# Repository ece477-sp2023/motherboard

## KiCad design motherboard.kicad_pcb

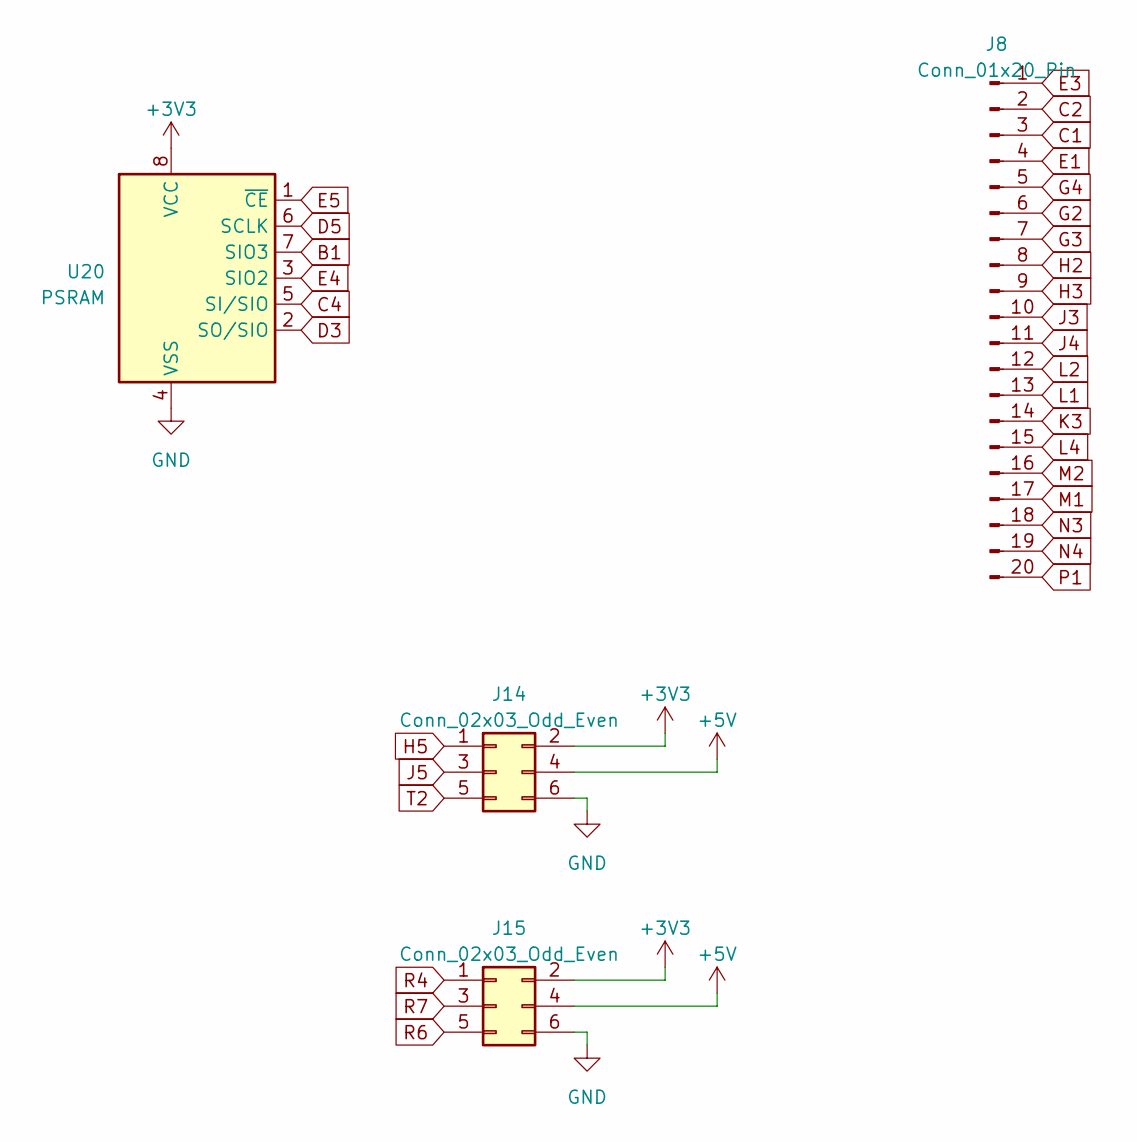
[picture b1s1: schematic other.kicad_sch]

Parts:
J8: Conn_01x20_Pin; PinHeader_2x10_P2.54mm_Vertical
J14, J15: Conn_02x03_Odd_Even; PinHeader_2x03_P2.54mm_Vertical
U20: PSRAM; SOIC-8_3.9x4.9mm_P1.27mm

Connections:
B1: U20.7 (SIO3); also elsewhere on the board
C1: J8.3; also elsewhere on the board
C2: J8.2; also elsewhere on the board
C4: U20.5 (SI/SIO); also elsewhere on the board
D3: U20.2 (SO/SIO); also elsewhere on the board
D5: U20.6 (SCLK); also elsewhere on the board
E1: J8.4; also elsewhere on the board
E3: J8.1; also elsewhere on the board
E4: U20.3 (SIO2); also elsewhere on the board
E5: U20.1 (~CE); also elsewhere on the board
G2: J8.6; also elsewhere on the board
G3: J8.7; also elsewhere on the board
G4: J8.5; also elsewhere on the board
H2: J8.8; also elsewhere on the board
H3: J8.9; also elsewhere on the board
H5: J14.1; also elsewhere on the board
J3: J8.10; also elsewhere on the board
J4: J8.11; also elsewhere on the board
J5: J14.3; also elsewhere on the board
K3: J8.14; also elsewhere on the board
L1: J8.13; also elsewhere on the board
L2: J8.12; also elsewhere on the board
L4: J8.15; also elsewhere on the board
M1: J8.17; also elsewhere on the board
M2: J8.16; also elsewhere on the board
N3: J8.18; also elsewhere on the board
N4: J8.19; also elsewhere on the board
P1: J8.20; also elsewhere on the board
R4: J15.1; also elsewhere on the board
R6: J15.5; also elsewhere on the board
R7: J15.3; also elsewhere on the board
T2: J14.5; also elsewhere on the board

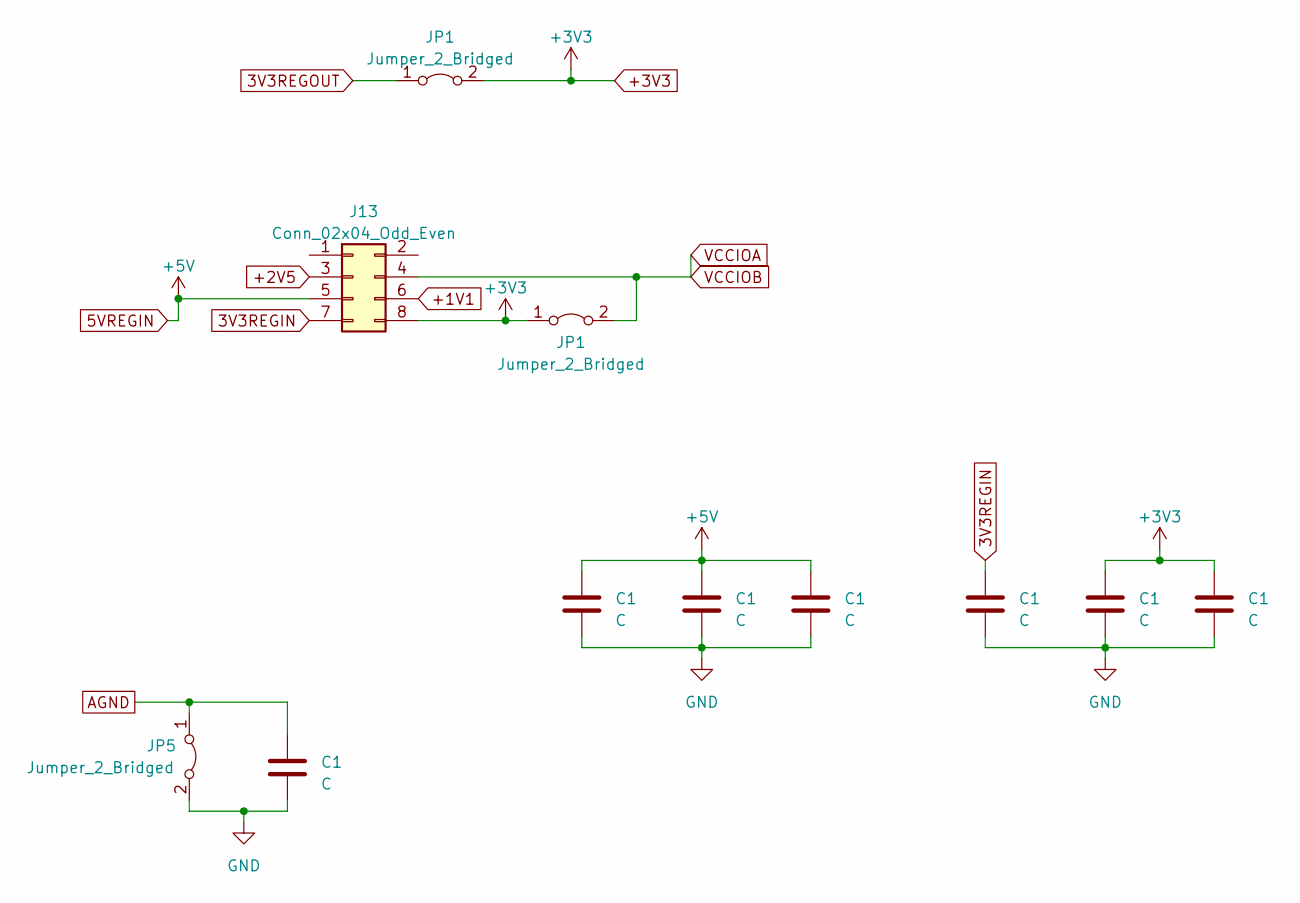
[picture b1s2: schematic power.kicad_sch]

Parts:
C1: C; C_0805_2012Metric
J13: Conn_02x04_Odd_Even; PinHeader_2x04_P2.54mm_Vertical
JP1, JP5: Jumper_2_Bridged; SolderJumper-2_P1.3mm_Bridged2Bar_RoundedPad1.0x1.5mm

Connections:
+1V1: J13.6; also elsewhere on the board
+2V5: J13.3; also elsewhere on the board

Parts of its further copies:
C2, C3, C4, C5, C6, C7: C; C_0805_2012Metric
JP3, JP4: Jumper_2_Bridged; SolderJumper-2_P1.3mm_Bridged2Bar_RoundedPad1.0x1.5mm

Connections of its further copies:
3V3REGOUT: JP4.1 (A); also elsewhere on the board

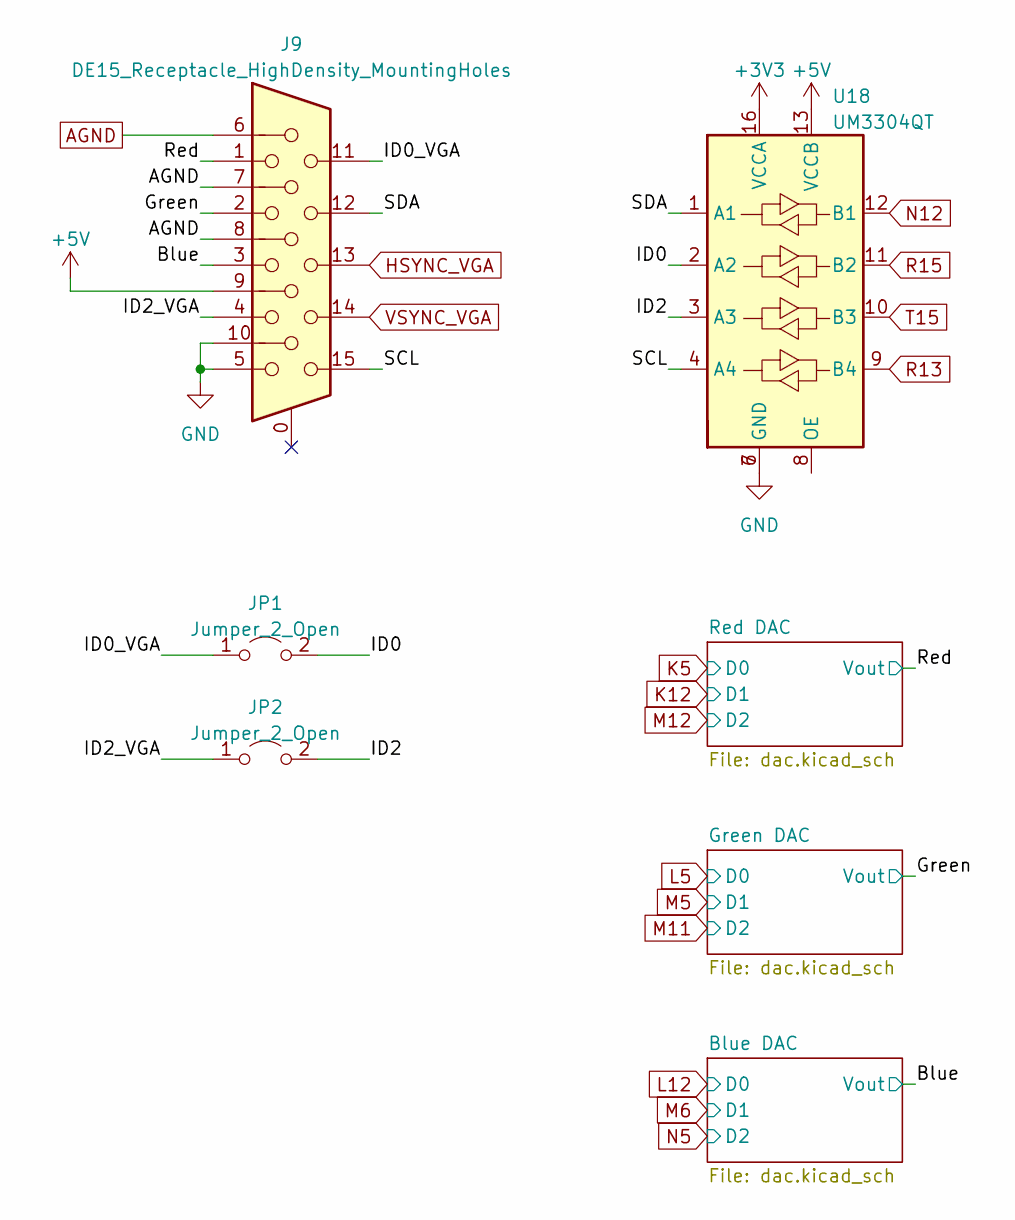
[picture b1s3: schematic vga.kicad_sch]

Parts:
J9: DE15_Receptacle_HighDensity_MountingHoles; DSUB-15-HD_Female_Horizontal_P2.29x1.98mm_EdgePinOffset3.03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
JP1, JP2: Jumper_2_Open; SolderJumper-2_P1.3mm_Open_TrianglePad1.0x1.5mm
U18: UM3304QT; QFN-16_1.8x2.6_Pitch0.4mm

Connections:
/VGA/Blue: J9.3; also elsewhere on the board
/VGA/Green: J9.2; also elsewhere on the board
/VGA/ID2_VGA: J9.4, JP2.1 (A)
/Voltage Shifting/5V Data: U18.10 (B3); also elsewhere on the board
OE: U18.8 (OE); also elsewhere on the board

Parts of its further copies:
U19: UM3304QT; QFN-16_1.8x2.6_Pitch0.4mm

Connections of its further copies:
N12: U19.12 (B1); also elsewhere on the board
R13: U19.9 (B4); also elsewhere on the board
R15: U19.11 (B2); also elsewhere on the board
T15: U19.10 (B3); also elsewhere on the board

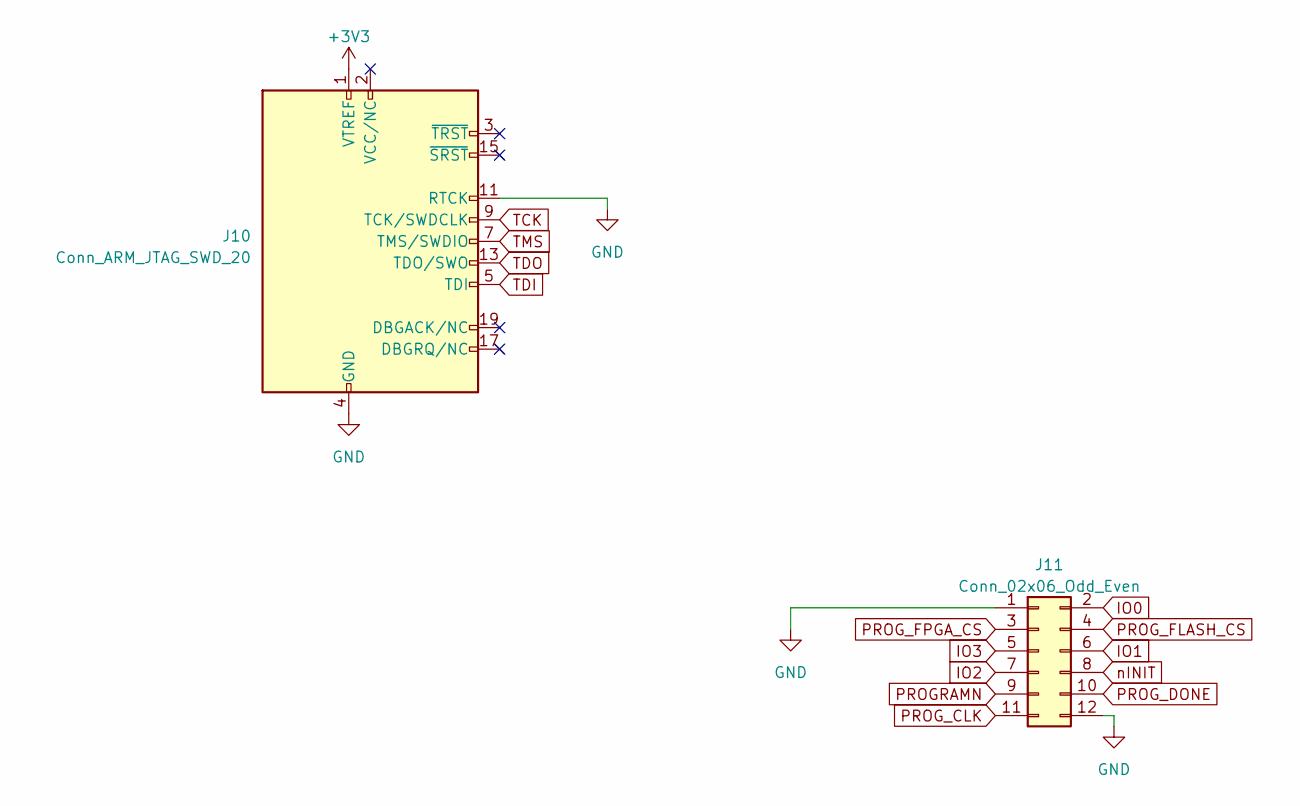
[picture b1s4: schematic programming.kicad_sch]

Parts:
J10: Conn_ARM_JTAG_SWD_20; PinHeader_2x10_P2.54mm_Vertical
J11: Conn_02x06_Odd_Even; PinHeader_2x06_P2.54mm_Vertical

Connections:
IO0: J11.2; also elsewhere on the board
IO1: J11.6; also elsewhere on the board
IO2: J11.7; also elsewhere on the board
IO3: J11.5; also elsewhere on the board
PROGRAMN: J11.9; also elsewhere on the board
PROG_CLK: J11.11; also elsewhere on the board
PROG_DONE: J11.10; also elsewhere on the board
PROG_FLASH_CS: J11.4; also elsewhere on the board
PROG_FPGA_CS: J11.3; also elsewhere on the board
TCK: J10.9 (TCK/SWDCLK); also elsewhere on the board
TDI: J10.5 (TDI); also elsewhere on the board
TDO: J10.13 (TDO/SWO); also elsewhere on the board
TMS: J10.7 (TMS/SWDIO); also elsewhere on the board
nINIT: J11.8; also elsewhere on the board

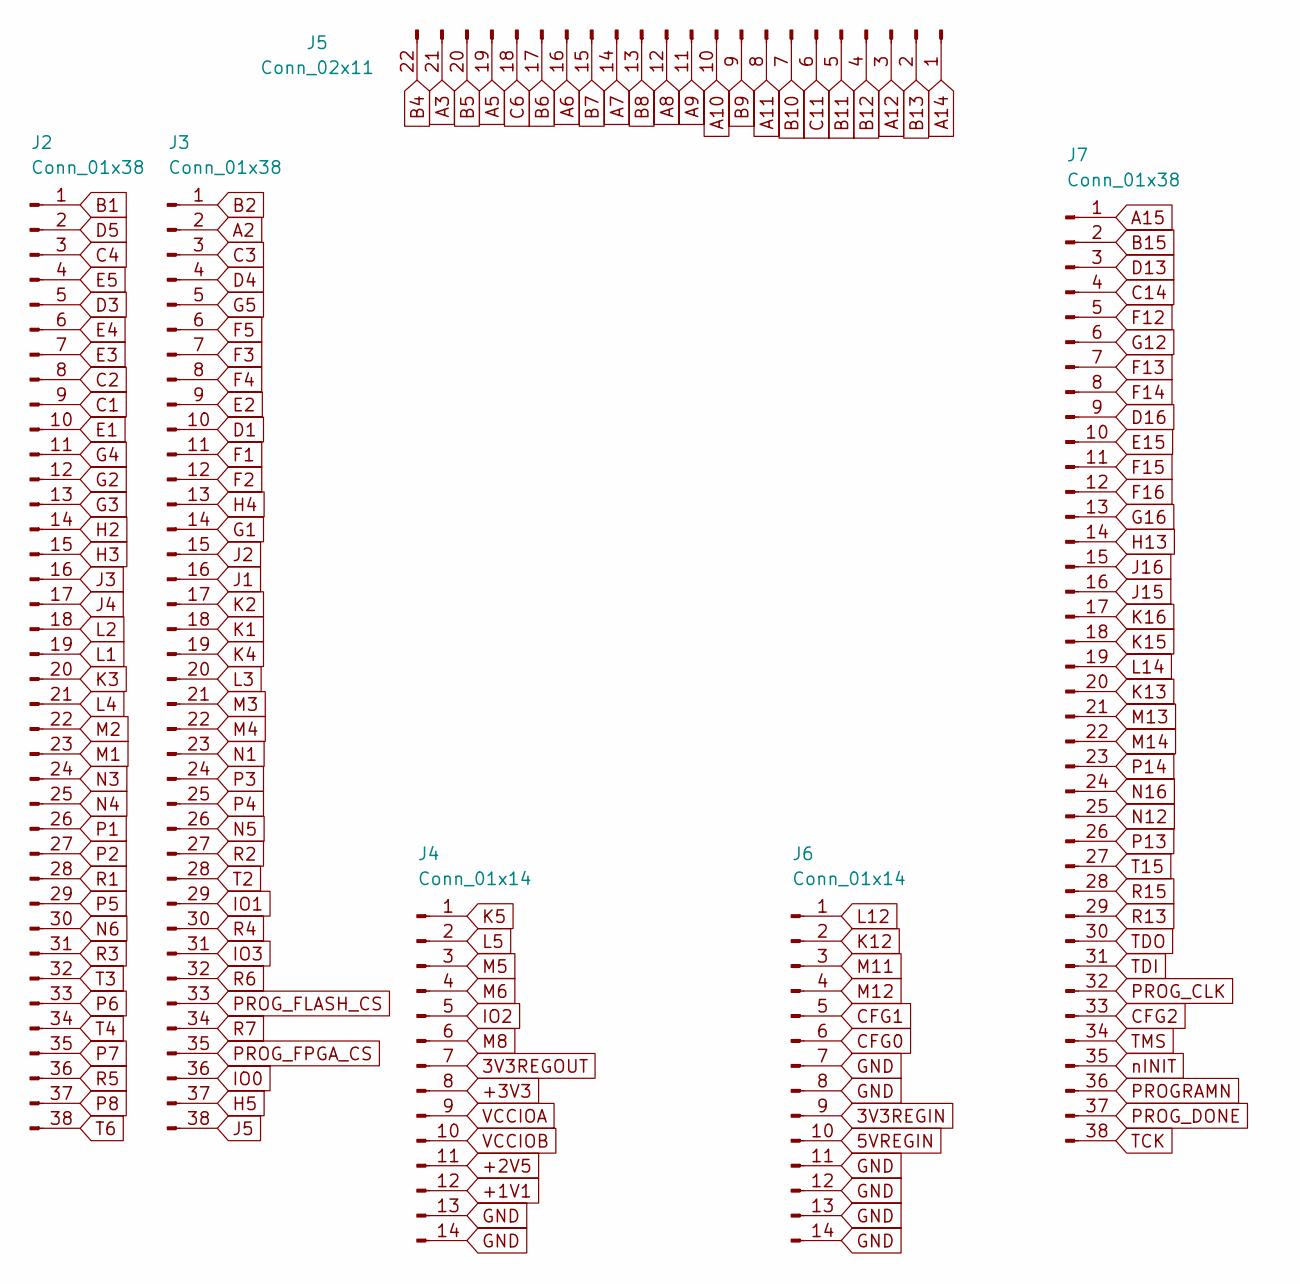
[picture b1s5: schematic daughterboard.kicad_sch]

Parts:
J2: Conn_01x38; PinHeader_1x38_P1.27mm_Vertical
J3, J7: Conn_01x38; PinHeader_2x19_P2.54mm_Vertical
J4, J6: Conn_01x14; PinHeader_2x07_P2.54mm_Vertical
J5: Conn_02x11; PinHeader_2x11_P2.54mm_Vertical

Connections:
3V3REGOUT: J4.7; also elsewhere on the board
+1V1: J4.12; also elsewhere on the board
+2V5: J4.11; also elsewhere on the board
A2: J3.2; also elsewhere on the board
A3: J5.21; also elsewhere on the board
A5: J5.19; also elsewhere on the board
A6: J5.16; also elsewhere on the board
A7: J5.14; also elsewhere on the board
A8: J5.12; also elsewhere on the board
A9: J5.11; also elsewhere on the board
A10: J5.10; also elsewhere on the board
A11: J5.8; also elsewhere on the board
A12: J5.3; also elsewhere on the board
A14: J5.1; also elsewhere on the board
A15: J7.1; also elsewhere on the board
B1: J2.1; also elsewhere on the board
B2: J3.1; also elsewhere on the board
B4: J5.22; also elsewhere on the board
B5: J5.20; also elsewhere on the board
B6: J5.17; also elsewhere on the board
B7: J5.15; also elsewhere on the board
B8: J5.13; also elsewhere on the board
B9: J5.9; also elsewhere on the board
B10: J5.7; also elsewhere on the board
B11: J5.5; also elsewhere on the board
B12: J5.4; also elsewhere on the board
B13: J5.2; also elsewhere on the board
B15: J7.2; also elsewhere on the board
C1: J2.9; also elsewhere on the board
C2: J2.8; also elsewhere on the board
C3: J3.3; also elsewhere on the board
C4: J2.3; also elsewhere on the board
C6: J5.18; also elsewhere on the board
C11: J5.6; also elsewhere on the board
C14: J7.4; also elsewhere on the board
CFG0: J6.6
CFG1: J6.5
CFG2: J7.33
D1: J3.10; also elsewhere on the board
D3: J2.5; also elsewhere on the board
D4: J3.4; also elsewhere on the board
D5: J2.2; also elsewhere on the board
D13: J7.3; also elsewhere on the board
D16: J7.9; also elsewhere on the board
E1: J2.10; also elsewhere on the board
E2: J3.9; also elsewhere on the board
E3: J2.7; also elsewhere on the board
E4: J2.6; also elsewhere on the board
E5: J2.4; also elsewhere on the board
F1: J3.11; also elsewhere on the board
F2: J3.12; also elsewhere on the board
F3: J3.7; also elsewhere on the board
F4: J3.8; also elsewhere on the board
F5: J3.6; also elsewhere on the board
F12: J7.5; also elsewhere on the board
F13: J7.7; also elsewhere on the board
F15: J7.11; also elsewhere on the board
G1: J3.14; also elsewhere on the board
G2: J2.12; also elsewhere on the board
G3: J2.13; also elsewhere on the board
G4: J2.11; also elsewhere on the board
G5: J3.5; also elsewhere on the board
G16: J7.13; also elsewhere on the board
H2: J2.14; also elsewhere on the board
H3: J2.15; also elsewhere on the board
H4: J3.13; also elsewhere on the board
H5: J3.37; also elsewhere on the board
H13: J7.14; also elsewhere on the board
IO0: J3.36; also elsewhere on the board
IO1: J3.29; also elsewhere on the board
IO2: J4.5; also elsewhere on the board
IO3: J3.31; also elsewhere on the board
J1: J3.16; also elsewhere on the board
J2: J3.15; also elsewhere on the board
J3: J2.16; also elsewhere on the board
J4: J2.17; also elsewhere on the board
J5: J3.38; also elsewhere on the board
J15: J7.16; also elsewhere on the board
J16: J7.15; also elsewhere on the board
K1: J3.18; also elsewhere on the board
K2: J3.17; also elsewhere on the board
K3: J2.20; also elsewhere on the board
K4: J3.19; also elsewhere on the board
K5: J4.1; also elsewhere on the board
K13: J7.20; also elsewhere on the board
K15: J7.18; also elsewhere on the board
K16: J7.17; also elsewhere on the board
L1: J2.19; also elsewhere on the board
L2: J2.18; also elsewhere on the board
L3: J3.20; also elsewhere on the board
L4: J2.21; also elsewhere on the board
L5: J4.2; also elsewhere on the board
L12: J6.1; also elsewhere on the board
L14: J7.19; also elsewhere on the board
M1: J2.23; also elsewhere on the board
M2: J2.22; also elsewhere on the board
M3: J3.21; also elsewhere on the board
M4: J3.22; also elsewhere on the board
M5: J4.3; also elsewhere on the board
M6: J4.4; also elsewhere on the board
M8: J4.6
M11: J6.3; also elsewhere on the board
M12: J6.4; also elsewhere on the board
M13: J7.21; also elsewhere on the board
M14: J7.22; also elsewhere on the board
N1: J3.23; also elsewhere on the board
N3: J2.24; also elsewhere on the board
N4: J2.25; also elsewhere on the board
N5: J3.26; also elsewhere on the board
N6: J2.30
N12: J7.25; also elsewhere on the board
N16: J7.24; also elsewhere on the board
OE: J3.27; also elsewhere on the board
P1: J2.26; also elsewhere on the board
P2: J2.27
P3: J3.24; also elsewhere on the board
P4: J3.25; also elsewhere on the board
P5: J2.29
P6: J2.33
P7: J2.35
P8: J2.37
P13: J7.26; also elsewhere on the board
P14: J7.23; also elsewhere on the board
PROGRAMN: J7.36; also elsewhere on the board
PROG_CLK: J7.32; also elsewhere on the board
PROG_DONE: J7.37; also elsewhere on the board
PROG_FLASH_CS: J3.33; also elsewhere on the board
PROG_FPGA_CS: J3.35; also elsewhere on the board
R1: J2.28
R3: J2.31
R4: J3.30; also elsewhere on the board
R5: J2.36
R6: J3.32; also elsewhere on the board
R7: J3.34; also elsewhere on the board
R13: J7.29; also elsewhere on the board
R15: J7.28; also elsewhere on the board
T2: J3.28; also elsewhere on the board
T3: J2.32
T4: J2.34
T6: J2.38
T15: J7.27; also elsewhere on the board
TCK: J7.38; also elsewhere on the board
TDI: J7.31; also elsewhere on the board
TDO: J7.30; also elsewhere on the board
TMS: J7.34; also elsewhere on the board
nINIT: J7.35; also elsewhere on the board

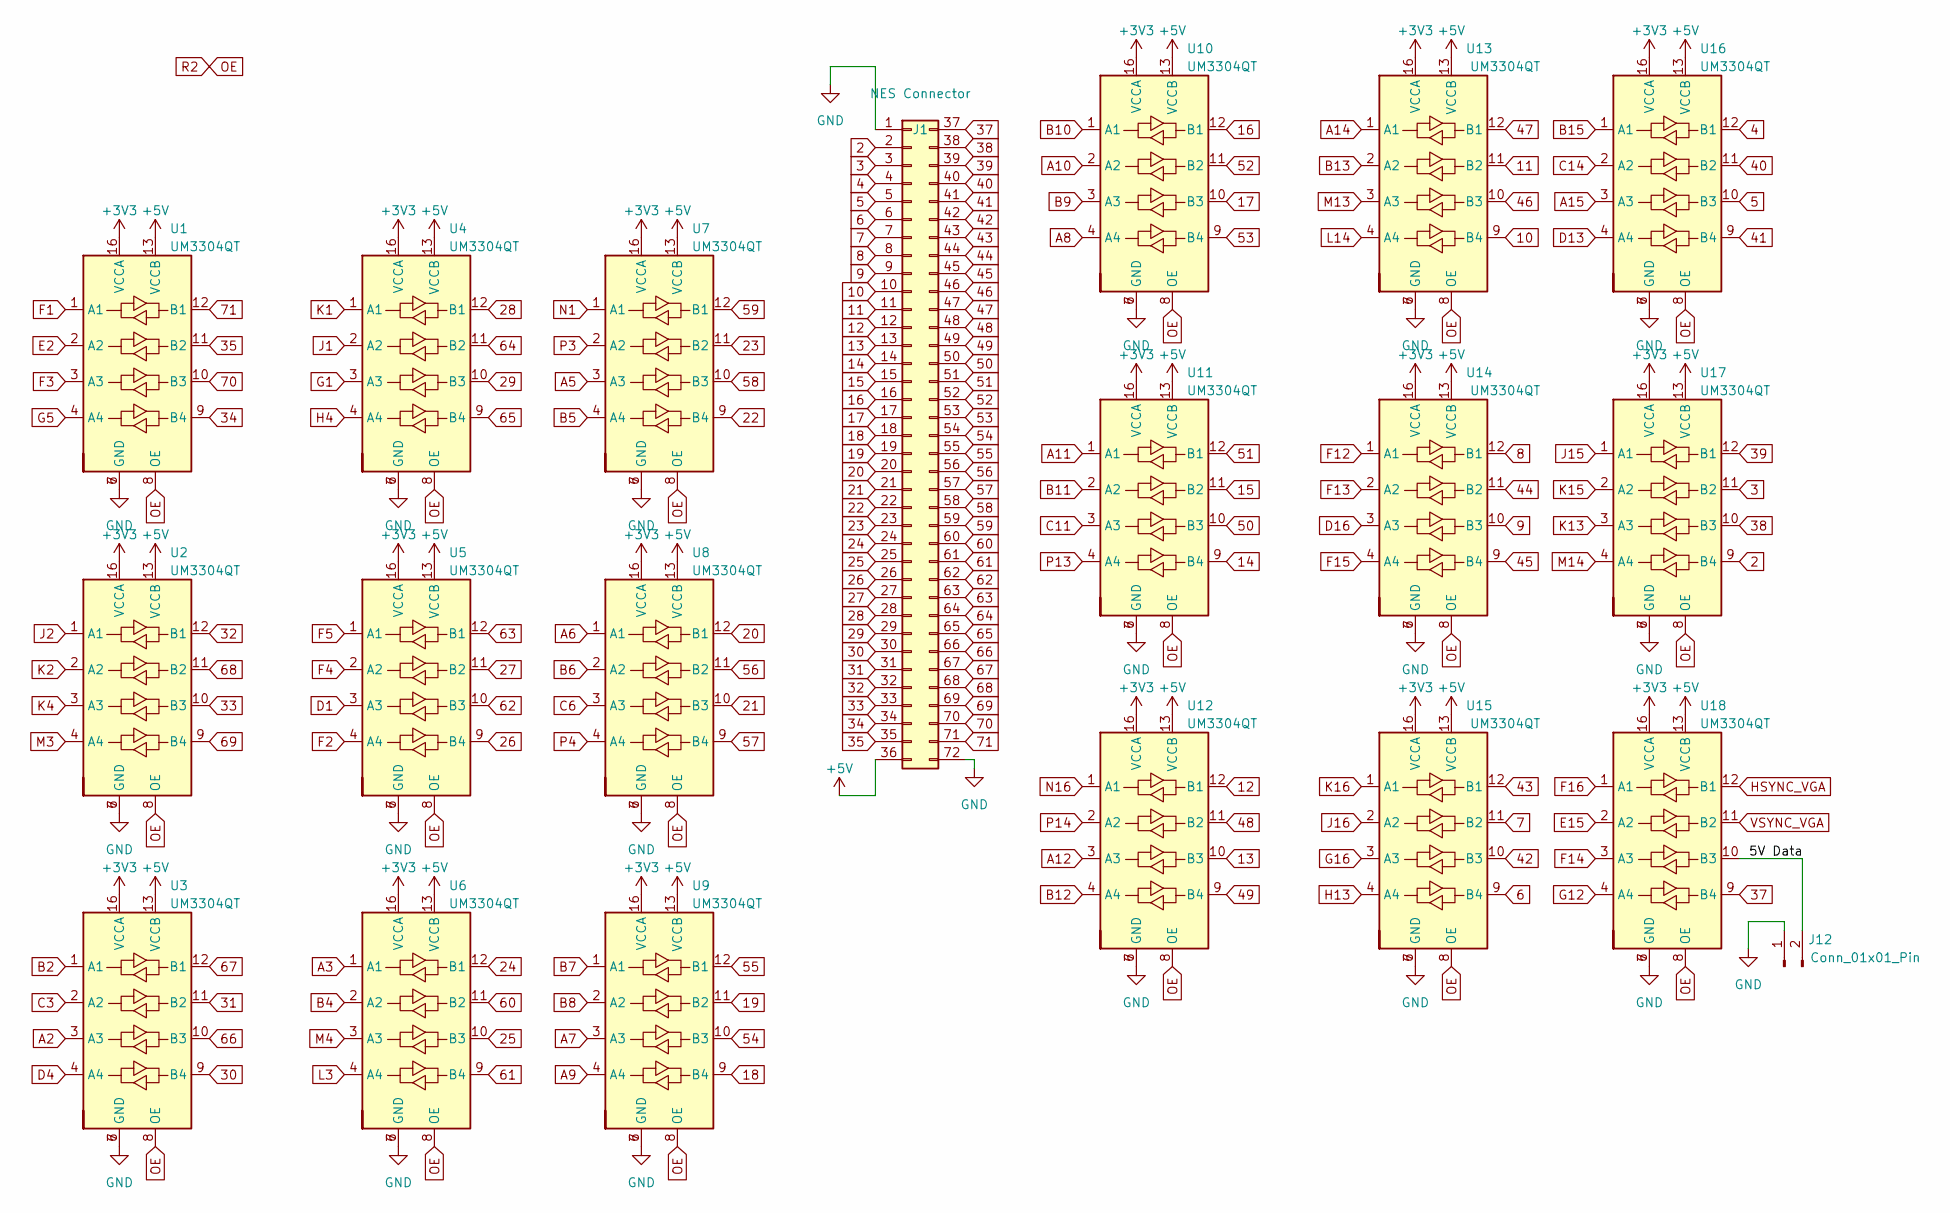
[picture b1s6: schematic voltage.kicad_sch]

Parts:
J1: NES Connector; NES_Connector
J12: Conn_01x01_Pin; PinHeader_1x02_P2.54mm_Vertical
U1, U2, U3, U4, U5, U6, U7, U8, U9, U10, U11, U12, U13, U14, U15, U16, U17, U18: UM3304QT; QFN-16_1.8x2.6_Pitch0.4mm

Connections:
2: J1.2, U17.9 (B4)
3: J1.3, U17.11 (B2)
4: J1.4, U16.12 (B1)
5: J1.5, U16.10 (B3)
6: J1.6, U15.9 (B4)
7: J1.7, U15.11 (B2)
8: J1.8, U14.12 (B1)
9: J1.9, U14.10 (B3)
10: J1.10, U13.9 (B4)
11: J1.11, U13.11 (B2)
12: J1.12, U12.12 (B1)
13: J1.13, U12.10 (B3)
14: J1.14, U11.9 (B4)
15: J1.15, U11.11 (B2)
16: J1.16, U10.12 (B1)
17: J1.17, U10.10 (B3)
18: J1.18, U9.9 (B4)
19: J1.19, U9.11 (B2)
20: J1.20, U8.12 (B1)
21: J1.21, U8.10 (B3)
22: J1.22, U7.9 (B4)
23: J1.23, U7.11 (B2)
24: J1.24, U6.12 (B1)
25: J1.25, U6.10 (B3)
26: J1.26, U5.9 (B4)
27: J1.27, U5.11 (B2)
28: J1.28, U4.12 (B1)
29: J1.29, U4.10 (B3)
30: J1.30, U3.9 (B4)
31: J1.31, U3.11 (B2)
32: J1.32, U2.12 (B1)
33: J1.33, U2.10 (B3)
34: J1.34, U1.9 (B4)
35: J1.35, U1.11 (B2)
38: J1.38, U17.10 (B3)
39: J1.39, U17.12 (B1)
40: J1.40, U16.11 (B2)
41: J1.41, U16.9 (B4)
42: J1.42, U15.10 (B3)
43: J1.43, U15.12 (B1)
44: J1.44, U14.11 (B2)
45: J1.45, U14.9 (B4)
46: J1.46, U13.10 (B3)
47: J1.47, U13.12 (B1)
48: J1.48, U12.11 (B2)
49: J1.49, U12.9 (B4)
50: J1.50, U11.10 (B3)
51: J1.51, U11.12 (B1)
52: J1.52, U10.11 (B2)
53: J1.53, U10.9 (B4)
54: J1.54, U9.10 (B3)
55: J1.55, U9.12 (B1)
56: J1.56, U8.11 (B2)
57: J1.57, U8.9 (B4)
58: J1.58, U7.10 (B3)
59: J1.59, U7.12 (B1)
60: J1.60, U6.11 (B2)
61: J1.61, U6.9 (B4)
62: J1.62, U5.10 (B3)
63: J1.63, U5.12 (B1)
64: J1.64, U4.11 (B2)
65: J1.65, U4.9 (B4)
66: J1.66, U3.10 (B3)
67: J1.67, U3.12 (B1)
68: J1.68, U2.11 (B2)
69: J1.69, U2.9 (B4)
70: J1.70, U1.10 (B3)
71: J1.71, U1.12 (B1)
/Voltage Shifting/5V Data: J12.2, U18.10 (B3)
A2: U3.3 (A3); also elsewhere on the board
A3: U6.1 (A1); also elsewhere on the board
A5: U7.3 (A3); also elsewhere on the board
A6: U8.1 (A1); also elsewhere on the board
A7: U9.3 (A3); also elsewhere on the board
A8: U10.4 (A4); also elsewhere on the board
A9: U9.4 (A4); also elsewhere on the board
A10: U10.2 (A2); also elsewhere on the board
A11: U11.1 (A1); also elsewhere on the board
A12: U12.3 (A3); also elsewhere on the board
A14: U13.1 (A1); also elsewhere on the board
A15: U16.3 (A3); also elsewhere on the board
B2: U3.1 (A1); also elsewhere on the board
B4: U6.2 (A2); also elsewhere on the board
B5: U7.4 (A4); also elsewhere on the board
B6: U8.2 (A2); also elsewhere on the board
B7: U9.1 (A1); also elsewhere on the board
B8: U9.2 (A2); also elsewhere on the board
B9: U10.3 (A3); also elsewhere on the board
B10: U10.1 (A1); also elsewhere on the board
B11: U11.2 (A2); also elsewhere on the board
B12: U12.4 (A4); also elsewhere on the board
B13: U13.2 (A2); also elsewhere on the board
B15: U16.1 (A1); also elsewhere on the board
C3: U3.2 (A2); also elsewhere on the board
C6: U8.3 (A3); also elsewhere on the board
C11: U11.3 (A3); also elsewhere on the board
C14: U16.2 (A2); also elsewhere on the board
D1: U5.3 (A3); also elsewhere on the board
D4: U3.4 (A4); also elsewhere on the board
D13: U16.4 (A4); also elsewhere on the board
D16: U14.3 (A3); also elsewhere on the board
E2: U1.2 (A2); also elsewhere on the board
F1: U1.1 (A1); also elsewhere on the board
F2: U5.4 (A4); also elsewhere on the board
F3: U1.3 (A3); also elsewhere on the board
F4: U5.2 (A2); also elsewhere on the board
F5: U5.1 (A1); also elsewhere on the board
F12: U14.1 (A1); also elsewhere on the board
F13: U14.2 (A2); also elsewhere on the board
F15: U14.4 (A4); also elsewhere on the board
G1: U4.3 (A3); also elsewhere on the board
G5: U1.4 (A4); also elsewhere on the board
G16: U15.3 (A3); also elsewhere on the board
H4: U4.4 (A4); also elsewhere on the board
H13: U15.4 (A4); also elsewhere on the board
J1: U4.2 (A2); also elsewhere on the board
J2: U2.1 (A1); also elsewhere on the board
J15: U17.1 (A1); also elsewhere on the board
J16: U15.2 (A2); also elsewhere on the board
K1: U4.1 (A1); also elsewhere on the board
K2: U2.2 (A2); also elsewhere on the board
K4: U2.3 (A3); also elsewhere on the board
K13: U17.3 (A3); also elsewhere on the board
K15: U17.2 (A2); also elsewhere on the board
K16: U15.1 (A1); also elsewhere on the board
L3: U6.4 (A4); also elsewhere on the board
L14: U13.4 (A4); also elsewhere on the board
M3: U2.4 (A4); also elsewhere on the board
M4: U6.3 (A3); also elsewhere on the board
M13: U13.3 (A3); also elsewhere on the board
M14: U17.4 (A4); also elsewhere on the board
N1: U7.1 (A1); also elsewhere on the board
N16: U12.1 (A1); also elsewhere on the board
OE: U1.8 (OE), U2.8 (OE), U3.8 (OE), U4.8 (OE), U5.8 (OE), U6.8 (OE), U7.8 (OE), U8.8 (OE), U9.8 (OE), U10.8 (OE), U11.8 (OE), U12.8 (OE), U13.8 (OE), U14.8 (OE), U15.8 (OE), U16.8 (OE), U17.8 (OE), U18.8 (OE); also elsewhere on the board
P3: U7.2 (A2); also elsewhere on the board
P4: U8.4 (A4); also elsewhere on the board
P13: U11.4 (A4); also elsewhere on the board
P14: U12.2 (A2); also elsewhere on the board

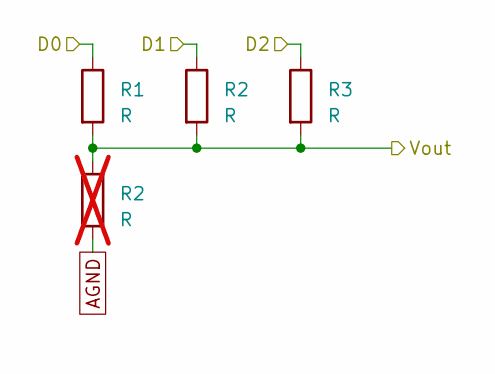
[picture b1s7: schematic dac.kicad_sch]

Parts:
R1, R3: R; R_0805_2012Metric
R2: R; R_0805_2012Metric; not fitted

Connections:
K5: R1.1; also elsewhere on the board
M12: R3.1; also elsewhere on the board

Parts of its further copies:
R5, R7, R8, R12, R13: R; R_0805_2012Metric; not fitted
R6, R9, R11, R14: R; R_0805_2012Metric

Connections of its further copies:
/VGA/Blue: R11.2, R12.1, R13.2, R14.2; also elsewhere on the board
/VGA/Green: R6.2, R7.1, R8.2, R9.2; also elsewhere on the board
L5: R6.1; also elsewhere on the board
L12: R11.1; also elsewhere on the board
M5: R8.1; also elsewhere on the board
M6: R13.1; also elsewhere on the board
M11: R9.1; also elsewhere on the board
N5: R14.1; also elsewhere on the board

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
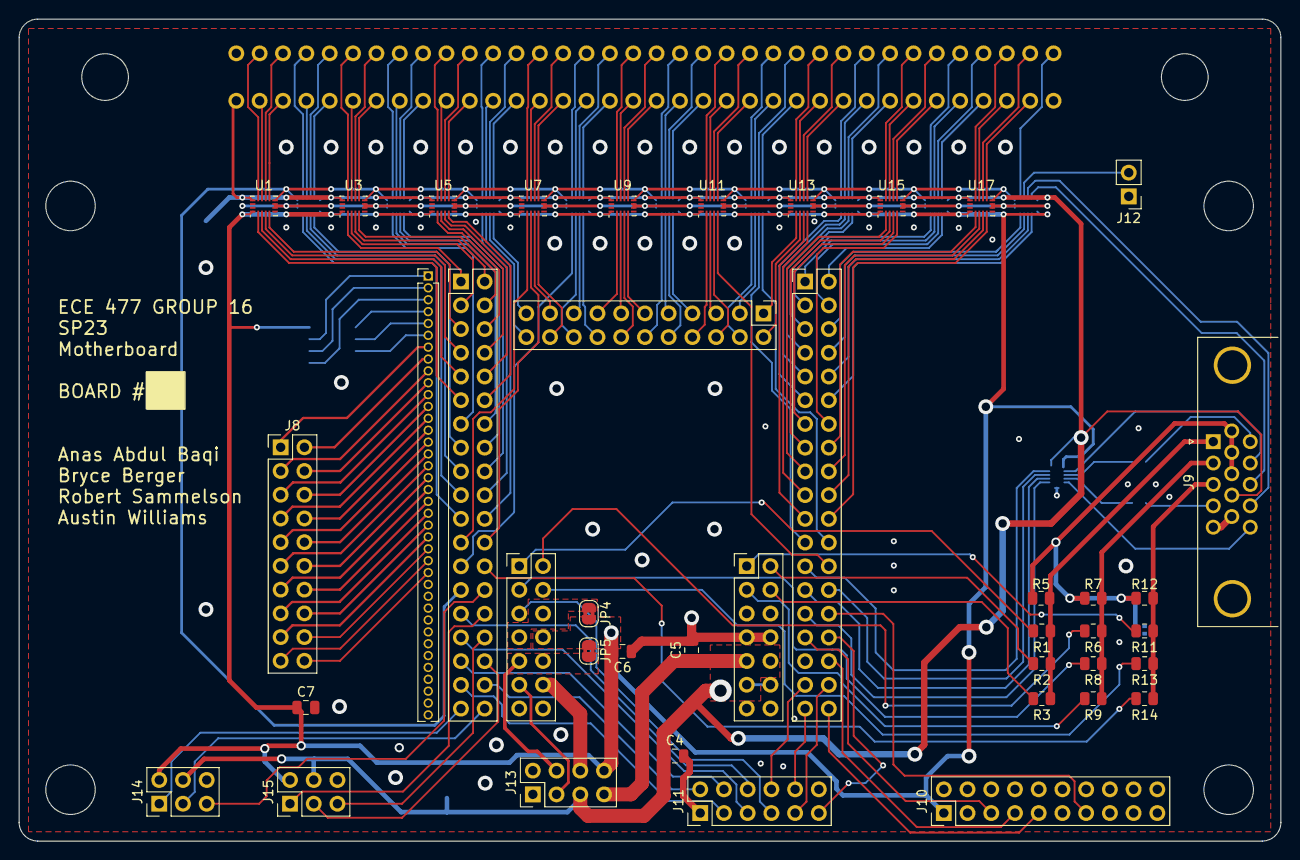
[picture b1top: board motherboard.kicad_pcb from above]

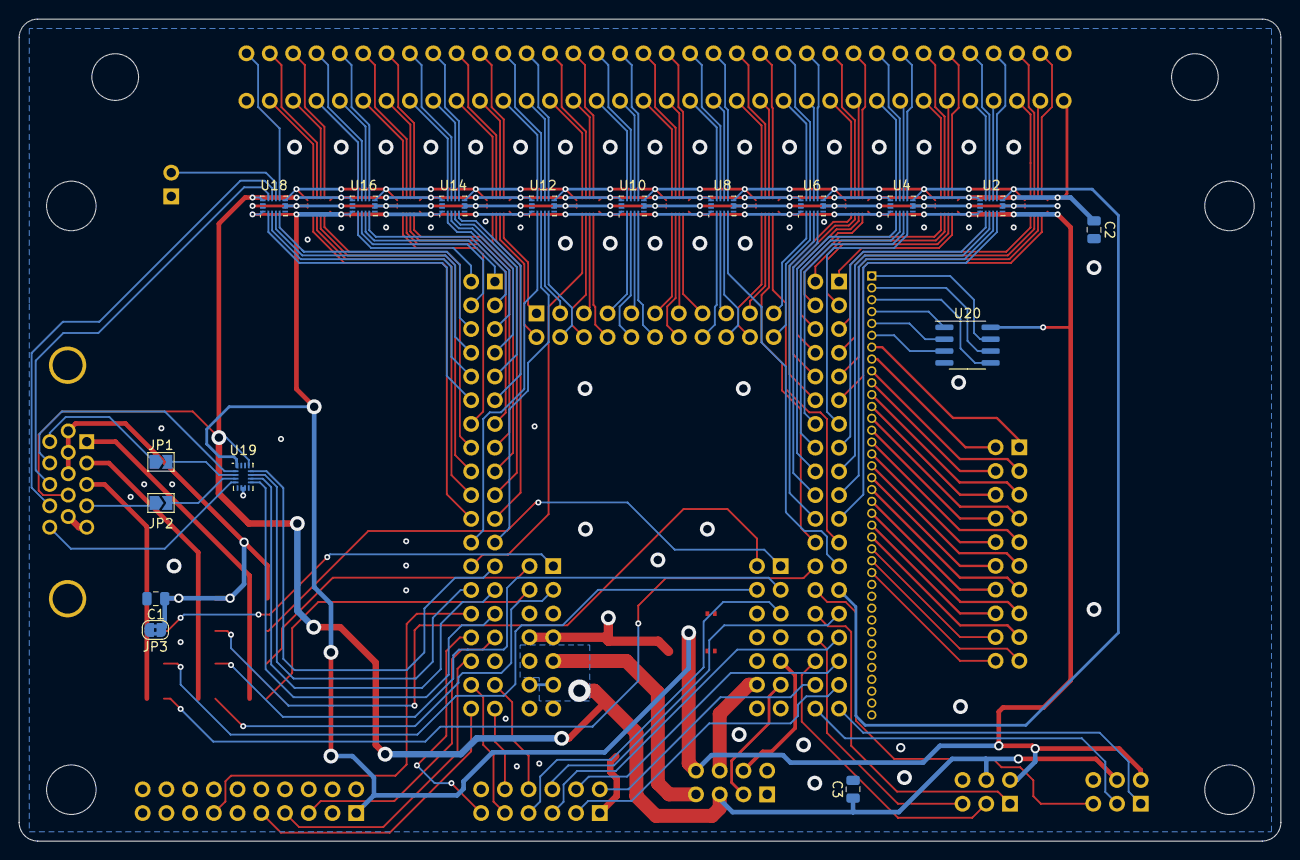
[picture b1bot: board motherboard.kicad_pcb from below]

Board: 2 copper layers, 135.1 x 88.0 mm, 59 parts (17 on the bottom side), 222 nets.

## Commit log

2023-03-09 Voltage conversion routing done
2023-03-09 Add gitignore
2023-03-14 Possibly finished PCB
2023-03-14 Add mounting holes
2023-03-14 Ready to order
